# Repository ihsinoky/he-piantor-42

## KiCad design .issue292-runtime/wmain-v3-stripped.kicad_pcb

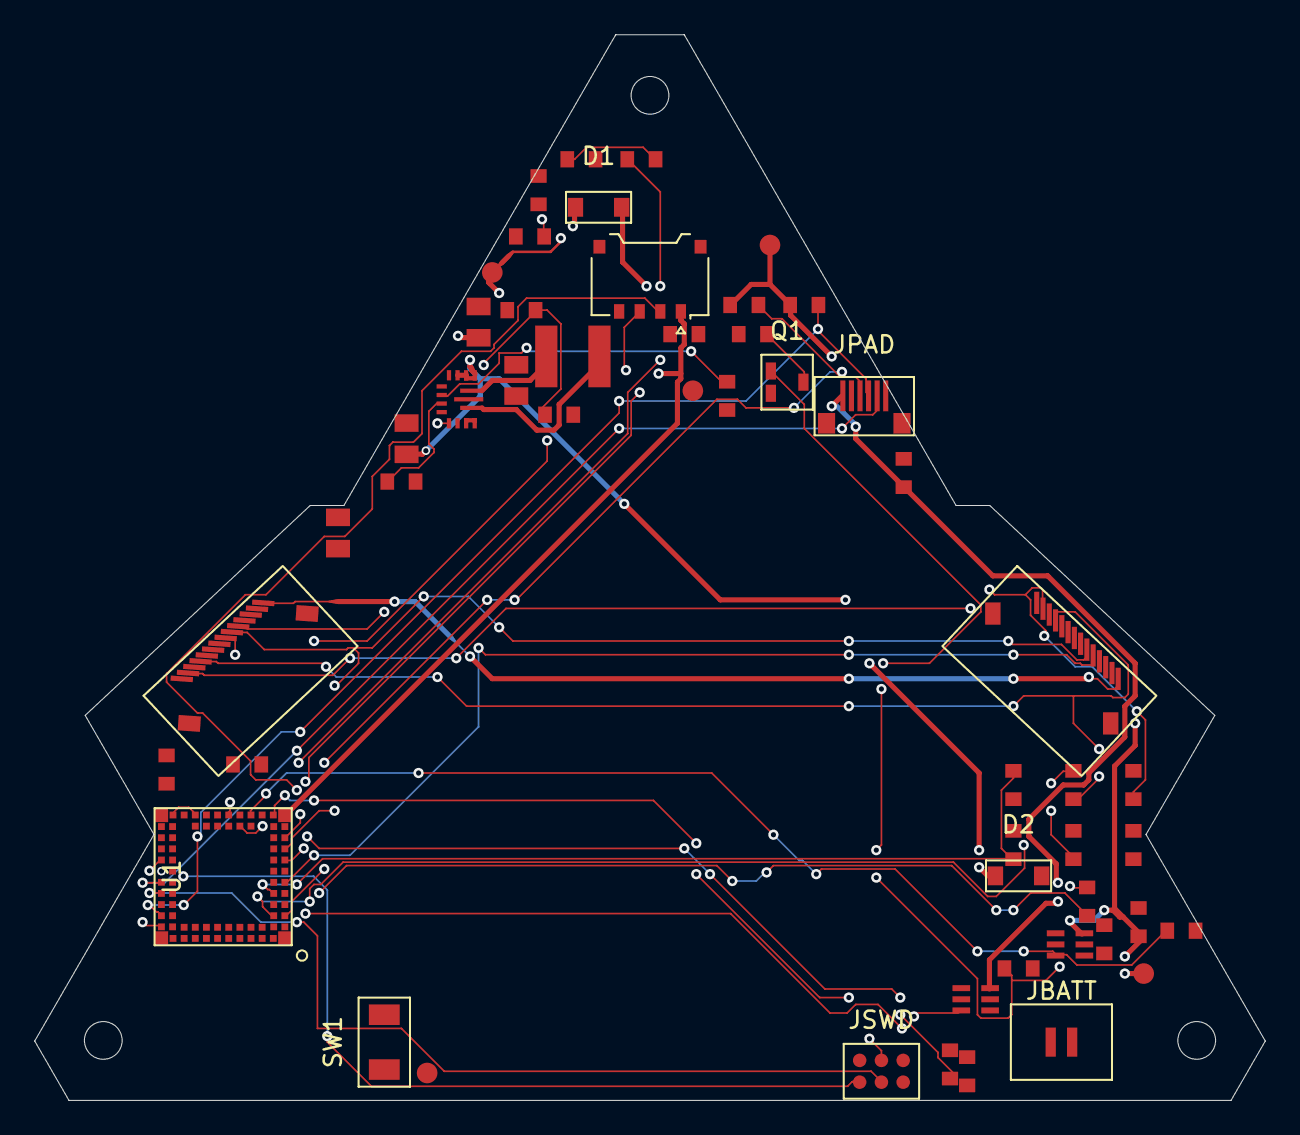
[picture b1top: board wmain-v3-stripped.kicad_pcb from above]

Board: 4 copper layers, 71.8 x 62.2 mm, 55 parts (0 on the bottom side), 41 nets.

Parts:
CFA: 1nF; C_0603
CFB: 1nF; C_0603
CFC: 1nF; C_0603
CHIN: 1uF; C_0603
CHOUT: 1uF; C_0603
CIN1, CIN2: 22uF; C_0805
COUT1, COUT2: 22uF; C_0805
CPOUT: 1uF; C_0603
CVAUX: 1uF; C_0603
CVCC1: 1uF; C_0603
CVCC2: 100nF; C_0603
CVS: 10nF; C_0603
D1, D2: PMEG4020; SOD-123
DLED: LED green; R_0603
H1, H2, H3: NPTH 2.2mm; MountingHole_2.2mm
J2, J3: FH12-14S-0.5SH(55); FH12-14S-0.5SH
J4: 781710004 (Fly link); Pico-EZmate_781710004
JBATT: B2B-XH-A; GH2
JPAD: FH12-6S-class FFC; FFC6_0.5mm_land
JSWD: TC2030-IDC-NL; TC2030-IDC-NL_Pads
L1: 1.5uH XFL4020-152MEC; XFL4020
Q1: 2N7002; SOT-23
RFA: 6.8k; R_0603
RFB: 6.8k; R_0603
RFB1: 49.9k; R_0603
RFB2: 16.0k; R_0603
RFC: 6.8k; R_0603
RLED: 1k; R_0603
RPD1, RPD2, RPD3: 100k; R_0603
RPG: 100k; R_0603
RPU1, RPU2: 4.7k; R_0603
RRST: 10k; R_0603
RV1, RV2: 1M; R_0603
RVG: 100k; R_0603
RVPD: 100k; R_0603
SW1: TACT (bring-up); TACT_2pad
TP1: TP VIN_IN; TestPoint
TP2: TP SYS_3V3; TestPoint
TP3: TP HALL_3V3; TestPoint
TP4: TP PAD_3V3; TestPoint
TP5: TP GND; TestPoint
U1: ISP1807-LR
U2: TPS63070RNMR
U3, U4: TPS22919DCKR

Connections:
ADC_A: CFA.1, RFA.2, U1.48
ADC_B: CFB.1, RFB.2, U1.46
ADC_C: CFC.1, RFC.2, U1.44
ANT_LINK: U1.20, U1.22
BTN: SW1.1, U1.34
CONV_PG: RPG.2, U2.2
FB_3V3: RFB1.2, RFB2.1, U2.5
GND: CFA.2, CFB.2, CFC.2, CHIN.2, CHOUT.2, CIN1.2, CIN2.2, COUT1.2, COUT2.2, CPOUT.2, CVAUX.2, CVCC1.2, CVCC2.2, CVS.2, DLED.2, J2.1, J2.3, J2.5, J2.7, J2.11, J2.13, J3.1, J3.3, J3.5, J3.7, J3.11, J3.13, J4.4, JBATT.2, JPAD.2, JPAD.6, JSWD.5, Q1.2, RFB2.2, RPD1.2, RPD2.2, RPD3.2, RVPD.2, SW1.2, TP5.1, U1.1, U1.7, U1.14, U1.16, U1.18, U1.21, U1.23, U1.24, U1.25, U1.31, U2.1, U2.4, U2.6, U2.10, U2.15, U3.2, U4.2
HALL_3V3: CHOUT.1, J2.14, J3.14, TP3.1, U3.6
HALL_PWR_EN: RPD1.1, U1.15, U3.3
LED_A: DLED.1, RLED.2
LED_DRV: RLED.1, U1.56
MUX_A0: J2.12, J3.12, U1.5
MUX_A1: J2.10, J3.10, U1.6
MUX_A2: J2.9, J3.9, U1.9
MUX_EN0: J2.8, RPD2.1, U1.17
MUX_EN1: J3.8, RPD3.1, U1.19
MUX_OUT_A: J2.6, J3.6, RFA.1
MUX_OUT_B: J2.4, J3.4, RFB.1
MUX_OUT_C: J2.2, J3.2, RFC.1
PAD_3V3: CPOUT.1, JPAD.1, RPU1.1, RPU2.1, TP4.1, U4.6
PAD_DR: JPAD.5, U1.29
PAD_EN: U1.33, U4.3
PAD_SCL: JPAD.3, RPU1.2, U1.3
PAD_SDA: JPAD.4, RPU2.2, U1.32
RESET_N: JSWD.3, RRST.2, U1.13
SWDCLK: JSWD.4, U1.30
SWDIO: JSWD.2, U1.28
SW_A: L1.1, U2.11
SW_B: L1.2, U2.9
SYS_3V3: CHIN.1, COUT1.1, COUT2.1, CVCC1.1, CVCC2.1, JSWD.1, RFB1.1, RPG.1, RRST.1, TP2.1, U1.26, U2.7, U2.8, U3.1, U4.1
USB_DM: J4.2, U1.10
USB_DP: J4.3, U1.8
VAUX: CVAUX.1, U2.3
VBAT+: D2.2, JBATT.1, RV1.1
VBAT_DRAIN: Q1.3, RV2.2
VBAT_GATE: Q1.1, RVG.2, RVPD.1
VBAT_GATE_M: RVG.1, U1.27
VBAT_SENSE: CVS.1, RV1.2, RV2.1, U1.40
VBUS: D1.2, J4.1, U1.12
VIN_IN: CIN1.1, CIN2.1, D1.1, D2.1, TP1.1, U2.12, U2.13, U2.14
